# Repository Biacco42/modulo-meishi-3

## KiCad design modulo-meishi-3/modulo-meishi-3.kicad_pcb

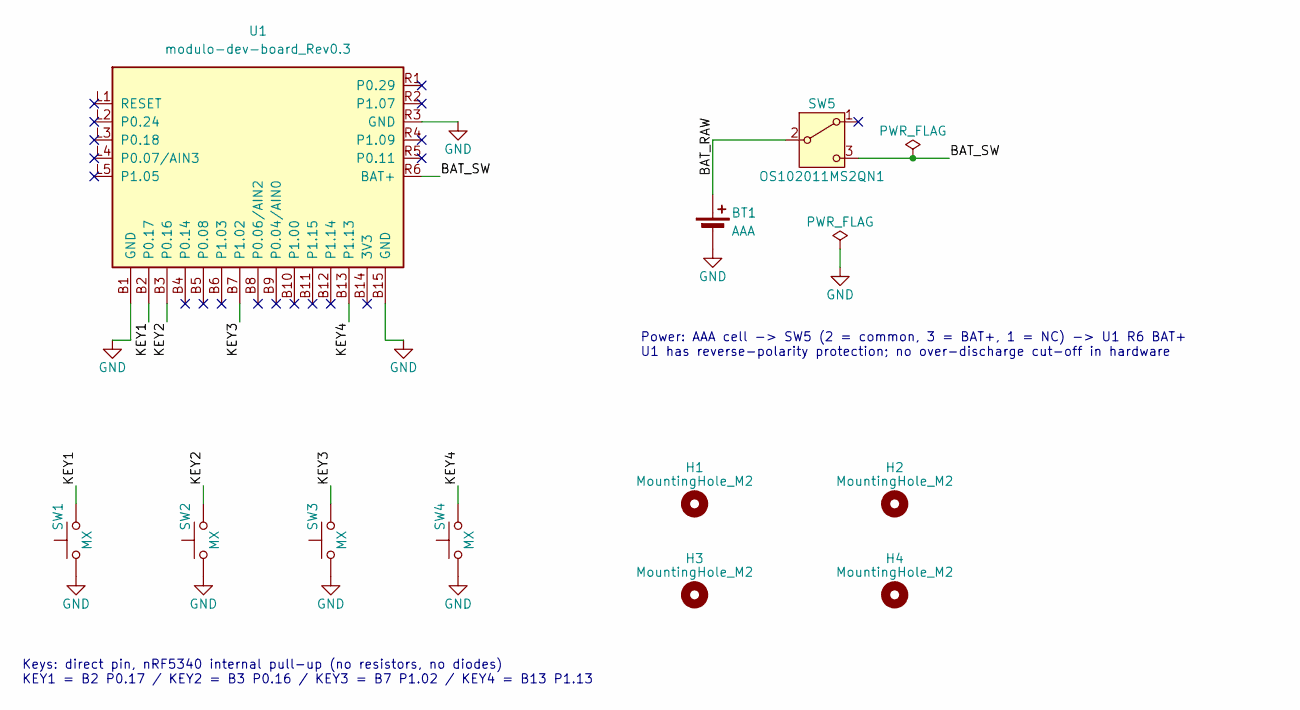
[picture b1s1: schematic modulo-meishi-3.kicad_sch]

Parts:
BT1: AAA; BatteryClip_Keystone_82_Pair_1xAAA; MPN 82 (x2)
H1, H2, H3, H4: MountingHole_M2; MountingHole_2.2mm_M2
SW1, SW2, SW3, SW4: MX; SW_Cherry_MX_1.00u_PCB
SW5: OS102011MS2QN1; SW_Slide_SPDT_Straight_CK_OS102011MS2Q; MPN OS102011MS2QN1
U1: modulo-dev-board_Rev0.3

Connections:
/BAT_RAW: BT1.1 (+), SW5.2 (B)
/BAT_SW: SW5.3 (C), U1.R6 (BAT+)
/KEY1: SW1.2, U1.B2 (P0.17)
/KEY2: SW2.2, U1.B3 (P0.16)
/KEY3: SW3.2, U1.B7 (P1.02)
/KEY4: SW4.2, U1.B13 (P1.13)
GND: BT1.2 (-), SW1.1, SW2.1, SW3.1, SW4.1, U1.B1 (GND), U1.B15 (GND), U1.R3 (GND)

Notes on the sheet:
Keys: direct pin, nRF5340 internal pull-up (no resistors, no diodes) KEY1 = B2 P0.17 / KEY2 = B3 P0.16 / KEY3 = B7 P1.02 / KEY4 = B13 P1.13
Power: AAA cell -> SW5 (2 = common, 3 = BAT+, 1 = NC) -> U1 R6 BAT+ U1 has reverse-polarity protection; no over-discharge cut-off in hardware

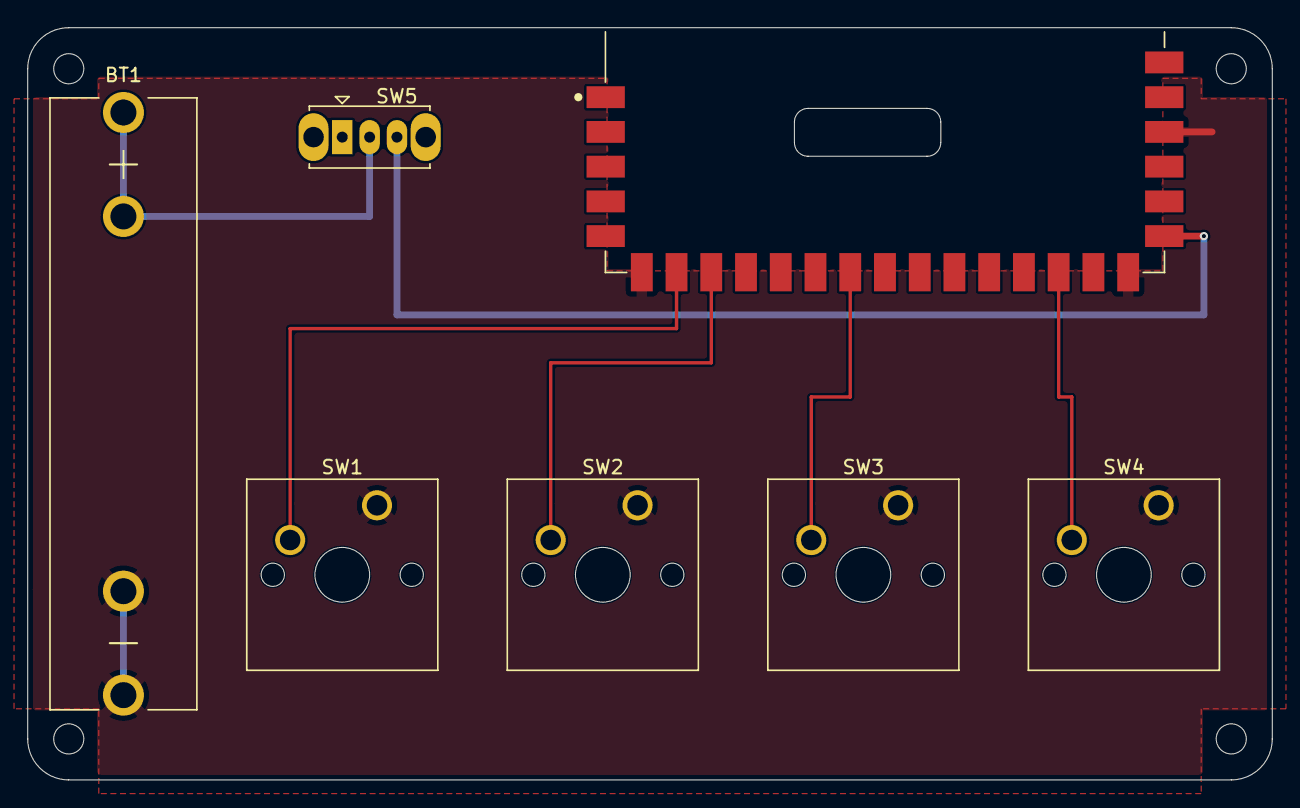
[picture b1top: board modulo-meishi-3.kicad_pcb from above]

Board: 2 copper layers, 91.0 x 55.0 mm, 11 parts (0 on the bottom side), 7 nets.
